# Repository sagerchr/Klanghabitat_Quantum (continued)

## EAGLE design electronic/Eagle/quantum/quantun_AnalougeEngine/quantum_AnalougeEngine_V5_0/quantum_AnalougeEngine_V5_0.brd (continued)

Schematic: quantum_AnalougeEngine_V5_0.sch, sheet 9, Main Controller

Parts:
C44, C73, C74, C75, C76, C77, C78, C79, C80, C81, C82, C83, C84, C85: 100 nF; C0603
C65, C66: 2.7 pF; C0603
C69, C70: 4.3 pF; C0603
C71, C72: 2.2 uF; C1206
DEBUG1, DEBUG2: TPTHT; THT_PIN
DISPLAY: 90814-0204; MOLEX_90814-0204
IC10: STM32F767ZIT6; QFP50P2200X2200X160-144N
IC12: ESDA6V1BC6; SOT95P280X145-6N
LD1: LED_YELOW_SMD; WL-SMCW_0603
LD2: LED_RED_SMD; WL-SMCW_0603
LD3: LED_GREEN_SMD; WL-SMCW_0603
PROG.: 90814-0204; MOLEX_90814-0204
R5, R6, R13: 680 R; R0603
R19, R78: 10 k; R0603
S1: PTS647SN50SMTR2LFS
X1: USB_B_CONNECTOR; SMARTPRJ_PN61729
Y1: NX3215SA-32.768K-STD-MUA-8; NX3215SA
Y2: NX3225GD-8MHZ-STD-CRA-3; RESC3226X100N

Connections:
8MHZ_CRYSTAL_A: C70.1, IC10.23 (PH0), Y2.1
8MHZ_CRYSTAL_B: C69.1, IC10.24 (PH1), Y2.2
32.768KHZ_A: C66.1, IC10.8 (PC14), Y1.1
32.768KHZ_B: C65.1, IC10.9 (PC15), Y1.2
+3V3: C73.1, C74.1, C75.1, C76.1, C77.1, C78.1, C79.1, C81.2, C82.2, C83.1, C84.1, C85.1, IC10.6 (VBAT), IC10.17 (VDD_1), IC10.30 (VDD_2), IC10.39 (VDD_3), IC10.52 (VDD_4), IC10.62 (VDD_5), IC10.72 (VDD_6), IC10.84 (VDD_7), IC10.95 (VDDUSB), IC10.108 (VDD_8), IC10.121 (VDDSDMMC), IC10.131 (VDD_9), IC10.144 (VDD_10); also elsewhere on the board
+3V3_SIG: IC10.47 (PB1); also elsewhere on the board
+5V_SIG: IC10.26 (PC0); also elsewhere on the board
+12V_SIG: IC10.42 (PA6); also elsewhere on the board
+15V_SIG: IC10.34 (PA0); also elsewhere on the board
-15V_SIG: IC10.37 (PA3); also elsewhere on the board
AGND: C44.1, C65.2, C66.2, C69.2, C70.2, C71.2, C72.2, C73.2, C74.2, C75.2, C76.2, C77.2, C78.2, C79.2, C80.1, C81.1, C82.1, C83.2, C84.2, C85.2, IC10.16 (VSS_1), IC10.31 (VSSA), IC10.38 (VSS_2), IC10.51 (VSS_3), IC10.61 (VSS_4), IC10.83 (VSS_5), IC10.94 (VSS_6), IC10.107 (VSS_7), IC10.120 (VSS_8), IC10.130 (VSS_9), IC12.2, IC12.5, PROG..4, R5.1, R6.1, R13.1, R78.2, S1.1, S1.2, X1.4; also elsewhere on the board
BOOT0: IC10.138 (BOOT0), R78.1
BUSY: IC10.88 (PG3); also elsewhere on the board
CHASIS: X1.P$1, X1.P$2; also elsewhere on the board
CS: IC10.123 (PD7); also elsewhere on the board
CS_DAC1: IC10.134 (PB4); also elsewhere on the board
CS_DAC2: IC10.135 (PB5); also elsewhere on the board
CV_A_B: IC10.113 (PC12); also elsewhere on the board
DAC_OUT1: IC10.40 (PA4); also elsewhere on the board
DAC_OUT2: IC10.41 (PA5); also elsewhere on the board
DB0: IC10.141 (PE0); also elsewhere on the board
DB1: IC10.142 (PE1); also elsewhere on the board
DB2: IC10.1 (PE2); also elsewhere on the board
DB3: IC10.2 (PE3); also elsewhere on the board
DB4: IC10.3 (PE4); also elsewhere on the board
DB5: IC10.4 (PE5); also elsewhere on the board
DB6: IC10.5 (PE6); also elsewhere on the board
DB7: IC10.58 (PE7); also elsewhere on the board
DB8: IC10.59 (PE8); also elsewhere on the board
DB9: IC10.60 (PE9); also elsewhere on the board
DB10: IC10.63 (PE10); also elsewhere on the board
DB11: IC10.64 (PE11); also elsewhere on the board
DB12: IC10.65 (PE12); also elsewhere on the board
DB13: IC10.66 (PE13); also elsewhere on the board
DB14: IC10.67 (PE14); also elsewhere on the board
DB15: IC10.68 (PE15); also elsewhere on the board
DEBUG1: DEBUG1.P$1, IC10.21 (PF9)
DEBUG2: DEBUG2.P$1, IC10.115 (PD1)
DIN_DAC: IC10.29 (PC3); also elsewhere on the board
FRST: IC10.122 (PD6); also elsewhere on the board
LD1: IC10.46 (PB0), LD1.2 (+)
LD2: IC10.137 (PB7), LD2.2 (+)
LD3: IC10.75 (PB14), LD3.2 (+)
unnamed: LD1.1 (-), R5.2
unnamed: IC10.101 (PA9), R19.1
unnamed: LD2.1 (-), R6.2
unnamed: C71.1, IC10.71 (VCAP_1)
unnamed: C72.1, IC10.106 (VCAP_2)
unnamed: C80.2, IC10.32 (VREF+), IC10.33 (VDDA)
unnamed: LD3.1 (-), R13.2
NRST: C44.2, IC10.25 (NRST), PROG..2, S1.3, S1.4; also elsewhere on the board
OS0: IC10.98 (PC8); also elsewhere on the board
OS1: IC10.99 (PC9); also elsewhere on the board
OS2: IC10.111 (PC10); also elsewhere on the board
PB12: IC10.73 (PB12); also elsewhere on the board
PD10: IC10.79 (PD10); also elsewhere on the board
PD11: IC10.80 (PD11); also elsewhere on the board
PD12: IC10.81 (PD12); also elsewhere on the board
RANGE: IC10.112 (PC11); also elsewhere on the board
RD: IC10.116 (PD2); also elsewhere on the board
RELAIS1: IC10.57 (PG1); also elsewhere on the board
RELAIS2: IC10.56 (PG0); also elsewhere on the board
RELAIS3: IC10.132 (PG15); also elsewhere on the board
RELAIS4: IC10.125 (PG10); also elsewhere on the board
RELAIS5: IC10.127 (PG12); also elsewhere on the board
RELAIS6: IC10.124 (PG9); also elsewhere on the board
RESET: IC10.87 (PG2); also elsewhere on the board
RMII_CRS_DV: IC10.43 (PA7); also elsewhere on the board
RMII_MDC: IC10.27 (PC1); also elsewhere on the board
RMII_MDIO: IC10.36 (PA2); also elsewhere on the board
RMII_REF_CLK: IC10.35 (PA1); also elsewhere on the board
RMII_RXD0: IC10.44 (PC4); also elsewhere on the board
RMII_RXD1: IC10.45 (PC5); also elsewhere on the board
RMII_TXD0: IC10.128 (PG13); also elsewhere on the board
RMII_TXD1: IC10.74 (PB13); also elsewhere on the board
RMII_TX_EN: IC10.126 (PG11); also elsewhere on the board
SCLK_DAC: IC10.69 (PB10); also elsewhere on the board
SWCLK: IC10.109 (PA14), PROG..1
SWDIO: IC10.105 (PA13), PROG..3
USART1_RX: IC10.76 (PB15); also elsewhere on the board
USART1_TX: IC10.136 (PB6); also elsewhere on the board
USART3_RX: IC10.77 (PD8); also elsewhere on the board
USART3_TX: IC10.78 (PD9); also elsewhere on the board
USART6_RX: DISPLAY.2, IC10.97 (PC7); also elsewhere on the board
USART6_TX: DISPLAY.1, IC10.96 (PC6); also elsewhere on the board
USB_ID: IC10.102 (PA10)
USB_N: IC10.103 (PA11), IC12.3, X1.2
USB_OVERCURRENT: IC10.92 (PG7)
USB_P: IC10.104 (PA12), IC12.6, X1.3
USB_POWERSWITCHON: IC10.91 (PG6)
USB_SOF: IC10.100 (PA8)
USB_VBUS: IC12.1, R19.2, X1.1

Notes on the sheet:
prg.adapter
8 MHZ
debug LEDs
USB port
Main Controller
reset switch
32.768 kHz
diff pair
display adapter

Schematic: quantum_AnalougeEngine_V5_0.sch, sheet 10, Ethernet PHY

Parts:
C40, C100: 30 pF; C0603
C86, C87, C90, C92, C93, C94: 100 nF; C0603
C88: 1 uF; C0603
C89: 470 pF; C0603
C91: 10 uF; C1206
C101: 4.7 uF; C1206
IC6: LAN8742A-CZ-TR; QFN50P400X400X100-25N
IC13: USBLC6-4SC6; SOT95P280X145-6N
J1: GWLEX-SMT-S988G_Y; GWLEXSMTS988GY
R18, R20, R21, R23, R27, R85: 10 k; R0603
R22: 1k5; R0603
R24, R25, R26: 33 R; R0603
R29, R88, R89, R90: 75 R; R0603
R77: 12k1; R0603
R79, R80, R81, R82: 50 R; R0603
R83, R84: 270 R; R0603
R91: 0 R; R0603
T1: H1102NL; SOIC127P940X597-16N
Y3: ABLS2-25.000MHZ-D4YF-T; ABLS

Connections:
+3V3: C86.2, C87.2, C90.2, C91.1, C92.2, C93.2, C94.2, IC6.1 (VDD2A), IC6.9 (VDDIO), IC6.19 (VDD1A), IC13.5 (VBUS), R18.1, R20.1, R21.1, R22.1, R23.2, R79.2, R80.2, R81.2, R82.2, T1.2 (CT_1), T1.7 (CT_2); also elsewhere on the board
AGND: C40.1, C86.1, C87.1, C88.1, C89.1, C90.1, C91.2, C92.1, C93.1, C94.1, C100.1, IC6.25 (EP_VSS), IC13.2 (GND), R27.1, R77.2, R83.1, R84.1, R85.1; also elsewhere on the board
CHASIS: R91.1; also elsewhere on the board
LED1: IC6.3 (LED1/NINT/NPME/!REGOFF), J1.10 (YELLOW_A), R85.2
LED2: IC6.2 (LED2/NINT/NPME/!NINTSEL), J1.12 (GREEN_A)
unnamed: IC6.7 (RXD1/!MODE1), R18.2, R24.2
unnamed: IC6.8 (RXD0/!MODE0), R20.2, R25.2
unnamed: IC6.11 (CRS_DV/!MODE2), R21.2, R26.2
unnamed: IC6.10 (RXER/!PHYAD0), R27.2
unnamed: IC6.24 (RBIAS), R77.1
unnamed: C88.2, C89.2, IC6.6 (VDDCR)
unnamed: J1.1, T1.16 (TX+)
unnamed: J1.2, T1.14 (TX-)
unnamed: J1.3, T1.11 (RX+)
unnamed: J1.6, T1.9 (RX-)
unnamed: J1.11 (GREEN_K), R84.2
unnamed: J1.9 (YELLOW_K), R83.2
unnamed: C40.2, IC6.4 (XTAL2), Y3.1
unnamed: C100.2, IC6.5 (XTAL1/CLKIN), Y3.2
unnamed: J1.7, R29.2
unnamed: J1.8, R88.2
unnamed: R89.2, T1.12 (NC_4)
unnamed: R90.2, T1.15 (NC_6)
unnamed: C101.1, R29.1, R88.1, R89.1, R90.1
unnamed: C101.2, J1.MP1 (13), J1.MP2 (14), R91.2
NRST: IC6.15 (NRST); also elsewhere on the board
RD_N: IC6.22 (RXN), IC13.6 (I/O4), R82.1, T1.8 (RD-)
RD_P: IC6.23 (RXP), IC13.1 (I/O1), R81.1, T1.6 (RD+)
RMII_CRS_DV: R26.1; also elsewhere on the board
RMII_MDC: IC6.13 (MDC); also elsewhere on the board
RMII_MDIO: IC6.12 (MDIO), R22.2; also elsewhere on the board
RMII_REF_CLK: IC6.14 (NINT/REFCLKO), R23.1; also elsewhere on the board
RMII_RXD0: R25.1; also elsewhere on the board
RMII_RXD1: R24.1; also elsewhere on the board
RMII_TXD0: IC6.17 (TXD0); also elsewhere on the board
RMII_TXD1: IC6.18 (TXD1); also elsewhere on the board
RMII_TX_EN: IC6.16 (TXEN); also elsewhere on the board
TD_N: IC6.20 (TXN), IC13.4 (I/O3), R80.1, T1.3 (TD-)
TD_P: IC6.21 (TXP), IC13.3 (I/O2), R79.1, T1.1 (TD+)

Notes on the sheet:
Ethernet PHY
diff pair

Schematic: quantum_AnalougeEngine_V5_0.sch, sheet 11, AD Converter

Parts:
C41: 100 nF; C0603
C42, C51: 10 uF; C1206
C52, C59: 1 uF; C0603
IC11: AD7606BSTZ; QFP50P1200X1200X160-64N
R1, R4, R14, R35, R42, R65, R87: 10 k; R0603
R2, R3, R39, R45, R86: 100 k; R0603

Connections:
+3V3: R45.2; also elsewhere on the board
+3V3_SIG: R45.1, R65.2; also elsewhere on the board
+5V: C41.1, IC11.1 (AVCC_1), IC11.23 (VDRIVE), IC11.37 (AVCC_2), IC11.38 (AVCC_3), IC11.48 (AVCC_4), R1.2, R35.1, R86.2; also elsewhere on the board
+5V_SIG: R86.1, R87.2; also elsewhere on the board
+12V: R39.2; also elsewhere on the board
+12V_SIG: R39.1, R42.2; also elsewhere on the board
+15V_SIG: R3.1, R4.2; also elsewhere on the board
-15V_SIG: R1.1, R2.2; also elsewhere on the board
AGND: C41.2, C42.2, C51.2, C52.2, C59.2, IC11.2 (AGND_1), IC11.26 (AGND_2), IC11.40 (AGND_4), IC11.41 (AGND_5), IC11.43 (REFGND_1), IC11.46 (REFGND_2), IC11.47 (AGND_6), IC11.50 (V1GND), IC11.52 (V2GND), IC11.54 (V3GND), IC11.56 (V4GND), IC11.58 (V5GND), IC11.60 (V6GND), IC11.62 (V7GND), IC11.64 (V8GND), R4.1, R14.2, R42.1, R65.1, R87.1; also elsewhere on the board
BUSY: IC11.14 (BUSY); also elsewhere on the board
CS: IC11.13 (!CS); also elsewhere on the board
CV_A_B: IC11.9 (CONVST), IC11.10 (!WR); also elsewhere on the board
DB0: IC11.16 (DB0); also elsewhere on the board
DB1: IC11.17 (DB1); also elsewhere on the board
DB2: IC11.18 (DB2); also elsewhere on the board
DB3: IC11.19 (DB3); also elsewhere on the board
DB4: IC11.20 (DB4); also elsewhere on the board
DB5: IC11.21 (DB5); also elsewhere on the board
DB6: IC11.22 (DB6); also elsewhere on the board
DB7: IC11.24 (DB7/DOUTA); also elsewhere on the board
DB8: IC11.25 (DB8/DOUTB); also elsewhere on the board
DB9: IC11.27 (DB9/DOUTC); also elsewhere on the board
DB10: IC11.28 (DB10/DOUTD); also elsewhere on the board
DB11: IC11.29 (DB11/SDI); also elsewhere on the board
DB12: IC11.30 (DB12); also elsewhere on the board
DB13: IC11.31 (DB13); also elsewhere on the board
DB14: IC11.32 (DB14); also elsewhere on the board
DB15: IC11.33 (DB15); also elsewhere on the board
FRST: IC11.15 (FRSTDATA); also elsewhere on the board
L/M_IN(VCA1_IN): IC11.49 (V1); also elsewhere on the board
L/M_OUT(OUT_STAGE_LEFT)_BEFORE: IC11.57 (V5); also elsewhere on the board
L/M_OUT(VCA1_OUT): IC11.53 (V3); also elsewhere on the board
unnamed: IC11.6 (!PAR!/SER_SEL), R14.1
unnamed: IC11.34 (REF_SELECT), R35.2
unnamed: C42.1, IC11.44 (REFCAPA), IC11.45 (REFCAPB)
unnamed: C51.1, IC11.42 (REFIN/REFOUT)
unnamed: C52.1, IC11.36 (REGCAP_1)
unnamed: C59.1, IC11.39 (REGCAP_2)
OS0: IC11.3 (OS0); also elsewhere on the board
OS1: IC11.4 (OS1); also elsewhere on the board
OS2: IC11.5 (OS2); also elsewhere on the board
R/S_IN(VCA2_IN): IC11.51 (V2); also elsewhere on the board
R/S_OUT(OUT_STAGE_RIGHT)_BEFORE: IC11.59 (V6); also elsewhere on the board
R/S_OUT(VCA2_OUT): IC11.55 (V4); also elsewhere on the board
RANGE: IC11.8 (RANGE); also elsewhere on the board
RD: IC11.12 (!RD!/SCLK); also elsewhere on the board
RESET: IC11.11 (RESET); also elsewhere on the board
V+: R3.2; also elsewhere on the board
V-: R2.1; also elsewhere on the board

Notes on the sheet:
AD Converter
Signal Conditioning
ADC1_IN0
ADC1_IN3
ADC1_IN6
ADC1_IN9
ADC1_IN10

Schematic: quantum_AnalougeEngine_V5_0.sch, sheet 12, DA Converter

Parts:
C14, C19, C22, C24, C36, C48, C49, C95, C96, C97, C98: 100 nF; C0603
C31, C32, C33, C34, C39, C64, C99: 10 uF; C1206
IC2, IC3: DAC084S085CIMM_NOPB; SOP50P490X110-10N
IC7, IC14, IC15: TL072; SOIC8
R38, R41, R44, R64: 27 k; R0603
R40, R43, R63, R66: 160 k; R0603
R46, R58, R60, R61, R62, R67, R70, R71, R72, R74, R75: 10 k; R0603
R47, R76: 1k8; R0603
R59, R73: 56 k; R0603
R68: 20 k; R0603
R92, R93, R94, R95: 500 R; R0603
Z1: ZENER_DIODE_BZT; SODFL1608X65N

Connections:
0,5V_DAC: IC7.3 (+IN), IC14.3 (+IN), IC15.1 (OUT), IC15.2 (-IN)
1V_DAC: C22.1, C32.1, IC3.7 (VREFIN), IC15.6 (-IN), IC15.7 (OUT)
1V_DAC_UNBUFFERD: C19.1, C64.1, IC15.5 (+IN), R61.2, R68.1
2V_DAC_REF: R67.1, R68.2, Z1.1 (K)
+5V: C14.1, C24.1, C31.1, C33.1, C34.1, C36.1, IC2.1 (VA), IC2.7 (VREFIN), IC3.1 (VA); also elsewhere on the board
.: IC14.1 (OUT), R59.2, R72.2
...: IC7.1 (OUT), R71.2, R73.2
AGND: C14.2, C19.2, C22.2, C24.2, C31.2, C32.2, C33.2, C34.2, C36.2, C39.2, C48.2, C49.2, C64.2, C95.2, C96.2, C97.2, C98.2, C99.2, IC2.6 (GND), IC3.6 (GND), R46.1, R47.1, R58.1, R60.1, R76.1, Z1.2 (A); also elsewhere on the board
CS_DAC1: R94.2; also elsewhere on the board
CS_DAC2: R95.2; also elsewhere on the board
DAC2_OUT1(OFFSET_VCA1): C99.1, R74.2, R76.2; also elsewhere on the board
DAC2_OUT2(OFFSET_VCA2): C39.1, R47.2, R75.2; also elsewhere on the board
DAC2_OUT3: IC3.4 (VOUTC), R62.1
DAC2_OUT4: IC3.5 (VOUTD), R70.1
DIN_DAC: R93.2; also elsewhere on the board
E+_OUT_STAGE_LEFT: IC7.6 (-IN), IC7.7 (OUT); also elsewhere on the board
E+_OUT_STAGE_RIGHT: IC14.6 (-IN), IC14.7 (OUT); also elsewhere on the board
unnamed: IC2.2 (VOUTA), R38.2
unnamed: IC2.3 (VOUTB), R41.2
unnamed: IC2.4 (VOUTC), R44.2
unnamed: IC2.5 (VOUTD), R64.2
unnamed: IC3.2 (VOUTA), R74.1
unnamed: IC3.3 (VOUTB), R75.1
unnamed: IC7.5 (+IN), R46.2, R73.1
unnamed: IC14.5 (+IN), R58.2, R59.1
unnamed: IC15.3 (+IN), R60.2, R61.1
unnamed: IC7.2 (-IN), R62.2, R71.1
unnamed: IC14.2 (-IN), R70.2, R72.1
unnamed: IC2.10 (SCLK), IC3.10 (SCLK), R92.1
unnamed: IC2.8 (DIN), IC3.8 (DIN), R93.1
unnamed: IC2.9 (!SYNC), R94.1
unnamed: IC3.9 (!SYNC), R95.1
SCLK_DAC: R92.2; also elsewhere on the board
SYM1: R38.1, R40.2; also elsewhere on the board
SYM2: R41.1, R43.2; also elsewhere on the board
SYM3: R44.1, R63.2; also elsewhere on the board
SYM4: R64.1, R66.2; also elsewhere on the board
V+: C48.1, C95.1, C97.1, IC7.8 (V+), IC14.8 (V+), IC15.8 (V+), R67.2; also elsewhere on the board
V-: C49.1, C96.1, C98.1, IC7.4 (V-), IC14.4 (V-), IC15.4 (V-), R40.1, R43.1, R63.1, R66.1; also elsewhere on the board

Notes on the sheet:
DA Converter
creates CV: 0 75,75 mV +12,625 dB 128 0 mV 0 dB 255 -77,75 mV -12,625 dB
could offset the main VCA by 153 mV which means about + 25,5 dB! step size is approx. 0.1dB per bit
Output Gain Control
DAC Ref Voltages
main VCA offset
SYM THD VCAs

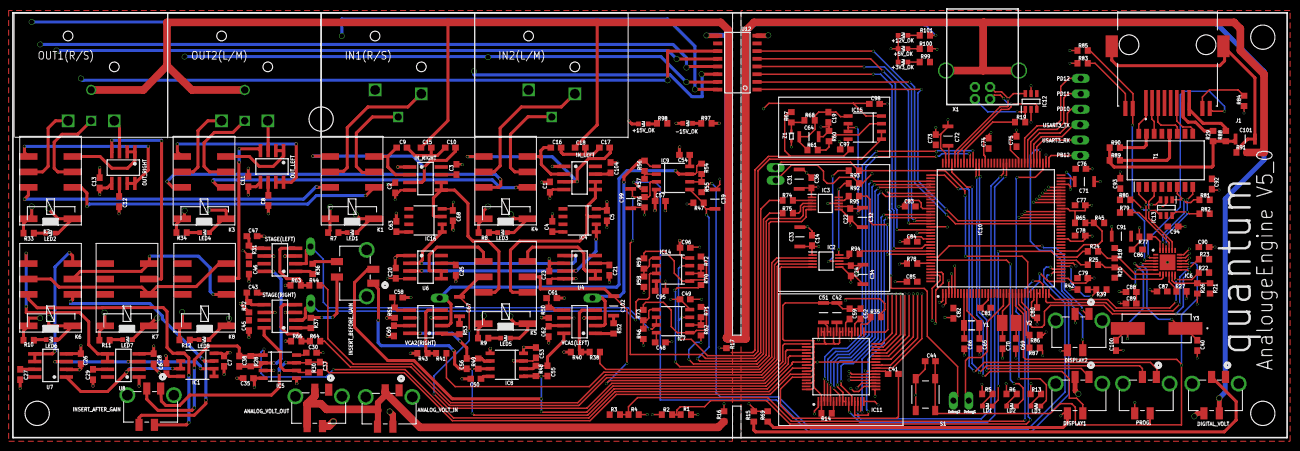
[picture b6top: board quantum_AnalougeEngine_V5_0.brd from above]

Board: 4 copper layers, 210.0 x 70.0 mm, 290 parts (0 on the bottom side), 241 nets.

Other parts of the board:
ANALOG_VOLT_IN: 90814-0204; MOLEX_90814-0204
ANALOG_VOLT_OUT: 90814-0204; MOLEX_90814-0204
DISPLAY1, DISPLAY2: 90814-0204; MOLEX_90814-0204
INSERT_AFTER_GAIN: 90814-0204; MOLEX_90814-0204
INSERT_BEFORE_GAIN: 90814-0204; MOLEX_90814-0204
TP03, TP04, TP05, TP06, TP07, TP08, TP09, TP10: TPTHT; THT_PIN

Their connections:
+5V: DISPLAY1.3, DISPLAY2.3; also elsewhere on the board
A_GND_TO_STAR: ANALOG_VOLT_IN.3, ANALOG_VOLT_IN.4, ANALOG_VOLT_OUT.3, ANALOG_VOLT_OUT.4; also elsewhere on the board
DIN_DAC: TP04.P$1; also elsewhere on the board
DISPLAY_GND_TO_STAR: DISPLAY1.4, DISPLAY2.4; also elsewhere on the board
L/M_OUT(OUT_STAGE_LEFT): INSERT_AFTER_GAIN.4; also elsewhere on the board
L/M_OUT(OUT_STAGE_LEFT)_BEFORE: INSERT_AFTER_GAIN.3; also elsewhere on the board
L/M_OUT(VCA1_OUT): INSERT_BEFORE_GAIN.3; also elsewhere on the board
unnamed 169: INSERT_BEFORE_GAIN.2; also elsewhere on the board
unnamed 170: INSERT_BEFORE_GAIN.4; also elsewhere on the board
PB12: TP05.P$1; also elsewhere on the board
PD10: TP08.P$1; also elsewhere on the board
PD11: TP09.P$1; also elsewhere on the board
PD12: TP10.P$1; also elsewhere on the board
R/S_OUT(OUT_STAGE_RIGHT): INSERT_AFTER_GAIN.2; also elsewhere on the board
R/S_OUT(OUT_STAGE_RIGHT)_BEFORE: INSERT_AFTER_GAIN.1; also elsewhere on the board
R/S_OUT(VCA2_OUT): INSERT_BEFORE_GAIN.1; also elsewhere on the board
SCLK_DAC: TP03.P$1; also elsewhere on the board
USART1_RX: DISPLAY2.2; also elsewhere on the board
USART1_TX: DISPLAY2.1; also elsewhere on the board
USART3_RX: TP06.P$1; also elsewhere on the board
USART3_TX: TP07.P$1; also elsewhere on the board
USART6_RX: DISPLAY1.2; also elsewhere on the board
USART6_TX: DISPLAY1.1; also elsewhere on the board
V+: ANALOG_VOLT_IN.1, ANALOG_VOLT_OUT.1; also elsewhere on the board
V-: ANALOG_VOLT_IN.2, ANALOG_VOLT_OUT.2; also elsewhere on the board
